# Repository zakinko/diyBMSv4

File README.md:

# diyBMS v4

Version 4 of the diyBMS

Do it yourself battery management system for Lithium ion battery packs/cells

More discussion [Open Energy Monitor Forum](https://community.openenergymonitor.org/c/hardware/diybms/53)

If you are looking for version 3 (obsolete) of this project take a look [here](https://github.com/stuartpittaway/diyBMS)

THIS REPOSITORY CONTAINS THE HARDWARE FOR THE SYSTEM

---

## About this branch — keeping the boards orderable

This is a fork of [stuartpittaway/diyBMSv4](https://github.com/stuartpittaway/diyBMSv4).
Every LCSC part number in every BOM here was checked against the JLCPCB parts API,
and **eight of the eleven boards could not be ordered as they stood** - parts at zero
stock, parts the API reports as discontinued, and on one board a BOM cell holding two
part numbers at once.  This branch fixes what can be fixed by changing a part number,
and says plainly where that is not enough.

**What is maintained**

* Part numbers that JLCPCB no longer stocks are replaced, where an equivalent exists
* Where the same part number also exists in the Basic library, it is used - Basic and
  Preferred parts carry no per-type setup fee
* Where no equivalent exists, the part is left alone and the reason is in the commit

**What is not**

* **Nothing here is tested on hardware.**  These are file-level changes checked
  against the schematic, the netlist, the datasheets and the parts API, and no
  further.  Reports from anyone who builds one are very welcome
* The circuits are not being redesigned.  Where a board has a weakness that needs a
  layout change - the ESP8266 controller has no decoupling capacitors at all, and no
  clamp on the ESP's RX line - it is written down, not fixed

**Two boards cannot be reproduced exactly, and are not pretended otherwise**

V440 and V450 both use AZ432 for their voltage reference.  Diodes discontinued it -
the datasheet is stamped OBSOLETE - USE AZ431L - and every SOT-23 shunt reference
still stocked is 1.240V rather than 1.250V.  On both boards that reference sets the
cell measurement, so substituting it shifts every reading by 0.8% with no warning.

D1 is therefore left as AZ432 on both.  Order the board without it and fit it by
hand; it is out of production but was made in volume and still turns up.  Anyone who
would rather have a current part than an exact V440/V450 should look at a revision
that designs AZ431L in and changes the firmware constant to match.

V400 is untouched for a different reason: its schematic carries no LCSC part numbers
at all and no BOM is generated from it.  Its parts are listed in a separate
spreadsheet, so making it orderable means building a BOM rather than editing one.

Upstream's own README follows unchanged.

---

# Videos on how to use and build

[YouTube playlist](https://youtube.com/playlist?list=PLHhwQCDPuRcZW3u0jJucsiCCsUbNbMy-c) for DIYBMS videos

[Building & ordering the PCB from JLCPCB](https://youtu.be/E1OS0ZOmOT8)

If you order a PCB, please use my affiliate link to help support this project [JLCPCB](https://jlcpcb.com/RSZ)

# Support

If you find the BMS useful, please consider buying me a beer, check out Patron for more information

https://patreon.com/StuartP

# HARDWARE

This repository contains the hardware designs, generally in KiCad format.  Unless you are changing the design, you don't need to use/install KiCad, just use the precompiled files.

The folder structure in the repository contains:

## Controller Designs
* ControllerCircuit - ESP32 controller board (newest design)
* ESP8266ControllerCircuit - [legacy] the circuit board for the legacy ESP8266 based controller

## Modules for Controller
* ModuleV490-AllInOne - Latest multi cell monitoring solution, recommended for 8 to 16S cell configurations.  No balancing, requires ModuleV490-PassiveBal passive balancer daughterboard if this is needed.
* ModuleV490-PassiveBal - daughter board for the V490 multi-cell monitoring solution, provides 200mA per cell balance current, heatsink and fan control.
* ModuleV450 - the latest SINGLE module design, using ATTINY1624 chip. Recommended for both hand soldering or mass production
* ModuleV440 - [legacy] the module circuit board V4.40, final board using ATTINY841 chip
* ModuleV400 - [legacy] the module circuit board V4.00, designed for easier hand soldering (larger parts)
* ModuleV421 - [legacy] the module circuit board V4.21, designed for mass production using JLCPCB assembly service

If you use this coupon code when you place a JLCPCB order

JLC-Stuart

and this link

https://jlcpcb.com/RSZ

you will get a discount and I get a very small amount of credit for every 30 orders, which helps to support the cost of prototyping new designs and adding new features.

### ESP32 Controller 

The latest version of the controller uses an ESP32 and supports CANBUS, RS485, SD CARD logging, relays, SSR outputs, multiple inputs, AVR programmer and much more.

Although the hardware is complete, not all features are usable from the software, this will be developed and improved over time to make use of the hardware.

[Bill of Materials](./ControllerCircuit/ComponentListBOM.md)

### Module V4.50

The latest version of the module hardware uses the ATTINY1624 chip - part of the tinyAVR2 range.

This board requires an UPDI programmer/device - see the instructions in the code repository for how to program the boards once built.

The parts are no smaller than 0805 size (about 2mm!) which is probably the smallest size you want to attempt to hand solder.

Specifications are similar to the V4.40 board.

### Module V4.40

V4.40 is the last board to use the ATTINY841 chip - V4.50 is the newest design if you are starting fresh.

In addition, the hardware has a higher balance current, fuse and TVS diode to help with voltage spikes.  
Most importantly, an external crystal has been added to the micro controller (attiny841) which means the device is more reliable in low voltage situations.

The balance current for V4.40 modules is as follows:
* 1.27A at 4.2V (5.35W)
* 1.21A at 4.0V (4.84W)
* 1.13A at 3.75V (4.26W)

The module is physically larger than previous modules, this aids heat dispersal but also features a "snap off" external temperature daughter board for use in cell temperature monitoring.

You will also need to order [these parts](./ModuleV440/HandAssemblyParts.md)

# CODE/SOFTWARE

Software and code for the modules and controller can now be found in a seperate repo

For the latest controller (ESP32)
[diyBMSv4ESP32](https://github.com/stuartpittaway/diyBMSv4ESP32)

For the legacy controller (ESP8266)
[diyBMSv4Code](https://github.com/stuartpittaway/diyBMSv4Code)

# WARNING

This is a DIY product/solution so don’t use this for safety critical systems or in any situation where there could be a risk to life.  

There is no warranty, it may not work as expected or at all.

The use of this project is done so entirely at your own risk.  It may involve electrical voltages which could kill - if in doubt, seek help.

The use of this project may not be compliant with local laws or regulations - if in doubt, seek help.

# License

This work is licensed under a Creative Commons Attribution-NonCommercial-ShareAlike 2.0 UK: England & Wales License.

https://creativecommons.org/licenses/by-nc-sa/2.0/uk/

You are free to:
* Share — copy and redistribute the material in any medium or format
* Adapt — remix, transform, and build upon the material
The licensor cannot revoke these freedoms as long as you follow the license terms.

Under the following terms:
* Attribution — You must give appropriate credit, provide a link to the license, and indicate if changes were made. You may do so in any reasonable manner, but not in any way that suggests the licensor endorses you or your use.
* Non-Commercial — You may not use the material for commercial purposes.
* ShareAlike — If you remix, transform, or build upon the material, you must distribute your contributions under the same license as the original.
* No additional restrictions — You may not apply legal terms or technological measures that legally restrict others from doing anything the license permits.

Notices:
You do not have to comply with the license for elements of the material in the public domain or where your use is permitted by an applicable exception or limitation.

No warranties are given. The license may not give you all of the permissions necessary for your intended use. For example, other rights such as publicity, privacy, or moral rights may limit how you use the material.

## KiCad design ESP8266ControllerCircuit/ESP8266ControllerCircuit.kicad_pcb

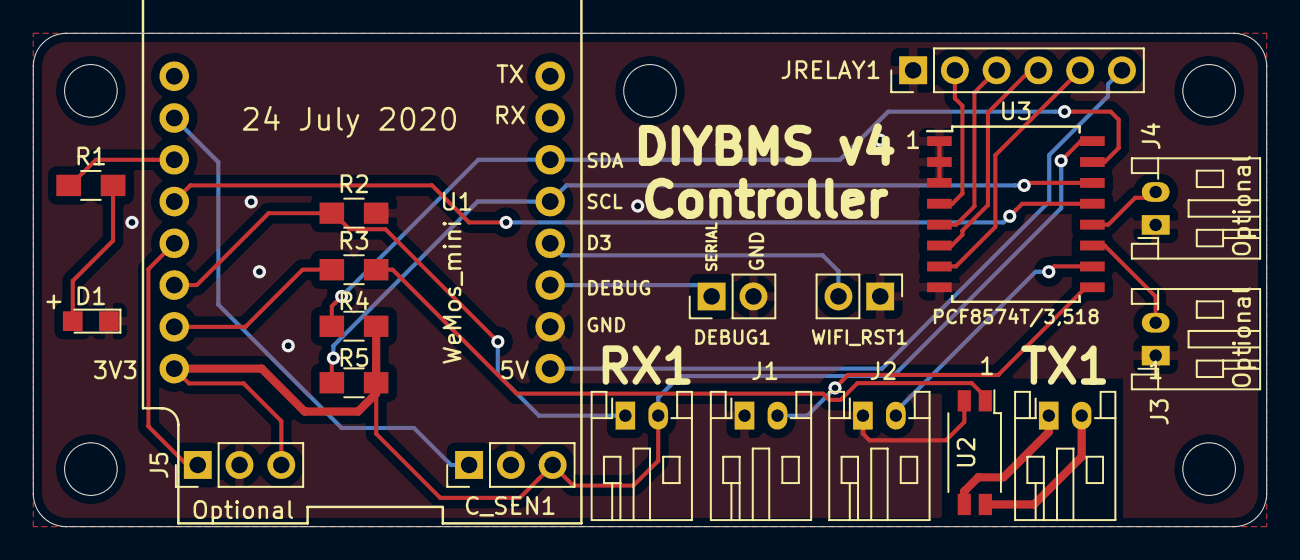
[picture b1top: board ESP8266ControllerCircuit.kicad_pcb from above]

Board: 2 copper layers, 75.0 x 30.0 mm, 20 parts (0 on the bottom side), 25 nets.

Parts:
C_SEN1: Current Sensor; Pin_Header_Straight_1x03_Pitch2.54mm
D1: COMMS; LED_0805
DEBUG1: Conn_01x02_Female; Pin_Header_Straight_1x02_Pitch2.54mm
J1, J2, J3, J4: Input; JST_PH_S2B-PH-K_02x2.00mm_Angled
J5: Optional; Pin_Header_Straight_1x03_Pitch2.54mm
JRELAY1: Conn_01x06_Male; Pin_Header_Straight_1x06_Pitch2.54mm
R1: 470R; R_0805_HandSoldering
R2: 2K2; R_0805_HandSoldering
R3: 220R; R_0805_HandSoldering
R4, R5: 4K7; R_0805_HandSoldering
RX1: Receive; JST_PH_S2B-PH-K_02x2.00mm_Angled
TX1: Transmit; JST_PH_S2B-PH-K_02x2.00mm_Angled
U1: WeMos_mini; wemos-d1-mini-with-pin-header
U2: EL3H7(B)(TA)-G; SOP-4_4.4x2.8mm_Pitch1.27mm
U3: PCF8574T/3,518; SOIC-16W_7.5x10.3mm_Pitch1.27mm
WIFI_RST1: WIFI RST; Pin_Header_Straight_1x02_Pitch2.54mm

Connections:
+3V3: C_SEN1.3, J5.3, R4.1, R5.1, RX1.2, U1.16, U3.16
+5V: JRELAY1.6, U1.1
GND: C_SEN1.2, D1.1, DEBUG1.2, J1.1, J2.1, J3.1, J4.1, J5.2, JRELAY1.1, R2.1, U1.2, U2.2, U3.1, U3.2, U3.3, U3.8, WIFI_RST1.1
unnamed: C_SEN1.1, U1.10
unnamed: D1.2, R1.1
unnamed: DEBUG1.1, U1.3
unnamed: J1.2, U3.9
unnamed: J2.2, U3.10
unnamed: J3.2, U3.11
unnamed: J4.2, U3.12
unnamed: J5.1, U1.13
unnamed: JRELAY1.2, U3.4
unnamed: JRELAY1.3, U3.5
unnamed: JRELAY1.4, U3.6
unnamed: JRELAY1.5, U3.7
unnamed: R1.2, U1.11
unnamed: R2.2, RX1.1, U1.14
unnamed: R3.1, U2.1
unnamed: R3.2, U1.15
unnamed: TX1.1, U2.3
unnamed: TX1.2, U2.4
unnamed: U1.4, WIFI_RST1.2
PCFINT: U1.12, U3.13
SCL: R5.2, U1.5, U3.14
SDA: R4.2, U1.6, U3.15

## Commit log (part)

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2025-07-25 Bump tj-actions/branch-names from 7.0.7 to 9.0.0 in /.github/workflows
    Bumps [tj-actions/branch-names](https://github.com/tj-actions/branch-names) from 7.0.7 to 9.0.0.
    - [Release notes](https://github.com/tj-actions/branch-names/releases)
    - [Changelog](https://github.com/tj-actions/branch-names/blob/main/HISTORY.md)
    - [Commits](https://github.com/tj-actions/branch-names/compare/v7.0.7...v9.0.0)
    ---
    updated-dependencies:

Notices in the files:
ESP8266ControllerCircuit/ESP8266ControllerCircuit.kicad_pcb:
©2019/2020 Stuart Pittaway
